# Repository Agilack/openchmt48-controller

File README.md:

# PickNPlace

Réingenierie d'une machine Pick and Place.

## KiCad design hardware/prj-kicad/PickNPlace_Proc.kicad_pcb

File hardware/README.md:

# pcb

Pinout
------

Diagram and table below show the details of boards connectors.

<table>
<tr><th>Connector</th><th>Signal</th><th>Type</th><th>MCU io</th>     <th>&nbsp</th> <th>Connector</th><th>Signal</th><th>Type</th><th>MCU io</th></tr>
<tr><td>J3-1</td><td>Light UP</td><td>NPN Output</td><td>PD10</td>    <td>&nbsp</td> <td>J8-1</td><td>Left nozzle pressure</td><td>Analog IN</td><td>PC5</td></tr>
<tr><td>J3-2</td><td>Light Down</td><td>NPN Output</td><td>PD9</td>   <td>&nbsp</td> <td>J8-2</td><td>Right nozzle pressure</td><td>Analog IN</td><td>PC4</td></tr>
<tr><td>J3-3</td><td>Valve Left</td><td>NPN Output</td><td>PD8</td>   <td>&nbsp</td> <td>J9-4</td><td>X-axis zero switch</td><td>Dry Contact</td><td>PC10</td></tr>
<tr><td>J3-4</td><td>Valve Right</td><td>NPN Output</td><td>PB15</td> <td>&nbsp</td> <td>J9-5</td><td>Y-axis zero switch</td><td>Dry Contact</td><td>PC11</td></tr>
<tr><td>J3-6</td><td>Needle</td><td>NPN Output</td><td>PB14</td>      <td>&nbsp</td> <td>&nbsp</td><td>&nbsp</td><td>&nbsp</td><td>&nbsp</td></tr>
<tr><td>J5-1</td><td>Pump Blow</td><td>NPN Output</td><td>PD12</td>   <td>&nbsp</td> <td>&nbsp</td><td>&nbsp</td><td>&nbsp</td><td>&nbsp</td></tr>
<tr><td>J5-4</td><td>Pump Vaccum</td><td>NPN Output</td><td>PD13</td> <td>&nbsp</td> <td>&nbsp</td><td>&nbsp</td><td>&nbsp</td><td>&nbsp</td></tr>
<tr><td>J6-4</td><td>Y encoder B-</td><td>Digital IN</td><td>PB13</td><td>&nbsp</td> <td>J1-4</td><td>X encoder B-</td><td>Digital IN</td><td>PE15</td></tr>
<tr><td>J6-5</td><td>Y encoder B+</td><td>Digital IN</td><td>PB13</td><td>&nbsp</td> <td>J1-5</td><td>X encoder B+</td><td>Digital IN</td><td>PE15</td></tr>
<tr><td>J6-6</td><td>Y encoder A-</td><td>Digital IN</td><td>PB12</td><td>&nbsp</td> <td>J1-6</td><td>X encoder A-</td><td>Digital IN</td><td>PE14</td></tr>
<tr><td>J6-7</td><td>Y encoder A+</td><td>Digital IN</td><td>PB12</td><td>&nbsp</td> <td>J1-7</td><td>X encoder A+</td><td>Digital IN</td><td>PE14</td></tr>
<tr><td>J12-1</td><td>Reels Step clock</td><td>Digital Output</td><td>PA2</td> <td>&nbsp</td> <td>J11-1</td><td>Nozzle 2 rotation clock</td><td>Digital Output</td><td>PB0</td>
<tr><td>J12-2</td><td>Reels Direction</td><td>Digital Output</td><td>PC2</td>  <td>&nbsp</td> <td>J11-2</td><td>Nozzle 2 rotation direction</td><td>Digital Output</td><td>PF14</td>
<tr><td>J12-3</td><td>Y step clock</td><td>Digital Output</td><td>PA1</td>     <td>&nbsp</td> <td>J11-3</td><td>Nozzle 1 rotation clock</td><td>Digital Output</td><td>PA7</td>
<tr><td>J12-4</td><td>Y Direction</td><td>Digital Output</td><td>PC1</td>      <td>&nbsp</td> <td>J11-4</td><td>Nozzle 1 rotation direction</td><td>Digital Output</td><td>PF15</td>
<tr><td>J12-5</td><td>X Step clock</td><td>Digital Output</td><td>PA0</td>     <td>&nbsp</td> <td>J11-5</td><td>Nozzle Z clock</td><td>Digital Output</td><td>PA6</td></tr>
<tr><td>J12-6</td><td>X Direction</td><td>Digital Output</td><td>PC0</td>      <td>&nbsp</td> <td>J11-6</td><td>Nozzle Z direction</td><td>Digital Output</td><td>PF13</td></tr>
<tr><td>J12-7</td><td>XYR enable</td><td>Digital Output</td><td>PA4</td>       <td>&nbsp</td> <td>J11-7</td><td>BCD enable</td><td>Digital Output</td><td>PA5</td></tr>
</table>

Changelog
---------

 * rev 0.2
   - Support for pumps control (vaccum and blow)
   - Support for logic outputs (valves, needle, lights)
   - Analog inputs for pressure sensors

 * rev 0.1
   - Support all stepper motors (X, Y, Z, reel, nozzle)
   - Inputs for encoders (X and Y axis)
   - Power supplies for head (7v, 5v)

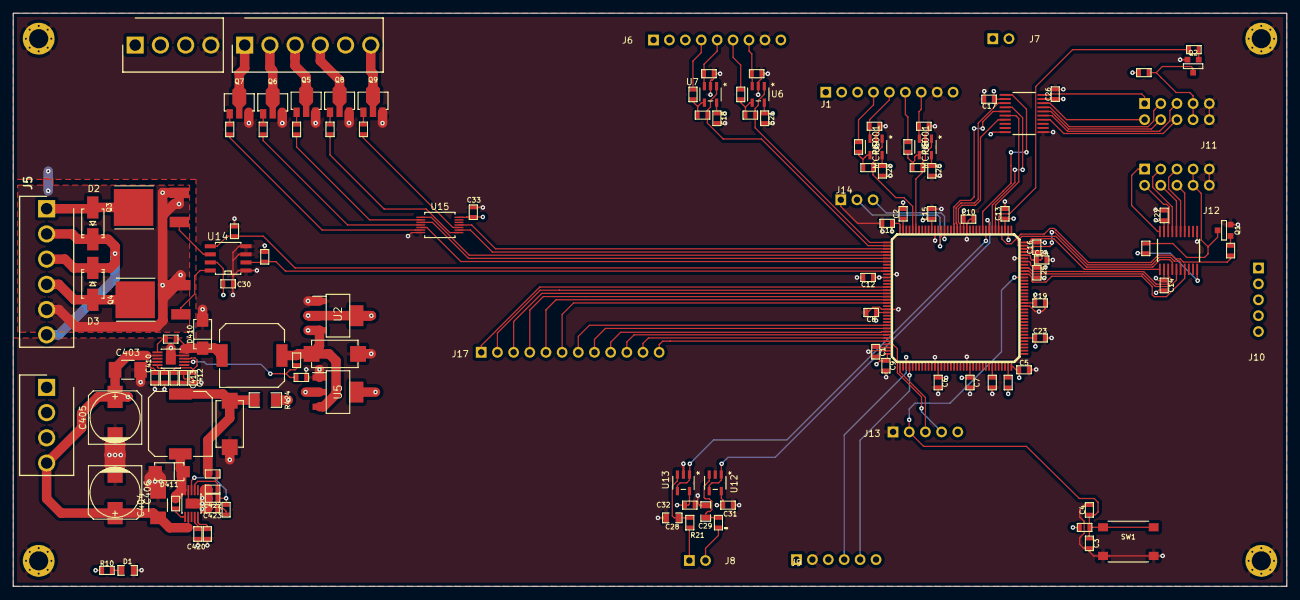
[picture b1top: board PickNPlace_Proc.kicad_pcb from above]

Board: 4 copper layers, 200.0 x 90.0 mm, 136 parts (0 on the bottom side), 124 nets.

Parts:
C1, C2: 2,2uF; SMD0603
C3, C30: 1uF; SMD0603
C4, C5, C6, C7, C8, C9, C10, C11, C12, C13, C14, C15, C16, C17, C18, C19, C20, C21, C22, C23, C24, C25, C26, C27, C31, C32, C33: 100nF; SMD0603
C28, C29: 1uF; SMD0805
C403, C404: 2,2uF; C_1210
C405, C406: 100uF; C_ALU_8x10.5
C410, C420: 10nF; SMD0603
C411, C421: 100nF; C_0603
C412, C422: n/a; SMD0603
C413, C423: 4,7nF; SMD0603
C414, C424: 220uF; C_TPB_D4
D1: LED; SMD0805
D2, D3: S1MLR3; D_SMA
D410, D411: MBRA340; DO214AC
FIX1, FIX2, FIX3, FIX4: CONN_1; FIX
J1, J6: Conn_01x09; 2_50___9pins
J2, J4: Conn_01x04; 3_96__4pins
J3, J5: Conn_01x06; B6P-VH_LF__SN_
J7, J8: Conn_01x02; 2_54___2pins
J9: Conn_01x06; 2_50___6pins
J10: Conn_01x05; 2_50___5pins
J11, J12: Conn_02x05_Odd_Even; 2_54____10pins__2rows
J13: Conn_01x05; 2_54____5pins
J14: Conn_01x03; 2_54___3pins
J17: Conn_01x12; 2_54____12pins
L410, L411: 27uH; I_MSS1048
Q1, Q2: Q_NPN; SOT23-3
Q3, Q4: Q_NMOS; TO-252-2Lead
Q5, Q6, Q7, Q8, Q9: NPN_2SCR533P_HZG; SOT-89
R1, R2, R3, R4, R5, R6, R7, R8, R9, R11, R12, R13, R14, R15, R16, R17, R18, R23, R24: 10k; R_0603
R10: 470; SMD0603
R19, R20, R21, R22: 1k; R_0603
R25, R26, R27, R28, R29: 470; R_0603
R410, R420: 100k; R_0603
R411, R421: 20k; R_0603
R412: 93,1k; R_0603
R413: 12k; R_0603
R422: 47k; R_0603
R423: 15k; R_0603
R424: 0; SMD1206
SW1: SW_PUSH; SW_430152043826
U1: STM32F745ZX; TQFP144
U2, U5: LM1117-5.0; TO261AA-LM1117
U3, U4: TPS54160A; MSOP10p
U6, U7, U8, U9, U12, U13: MCP6001; MCP6001T-I&slash_OT
U10, U11: TXS0108E-RGY; TSSOP20
U14: FAN3225TMX; SOIC-8
U15: SN74LVC07ADGVR; TVSOP-14_SN74LVC07ADGVR_copy

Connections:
+3V3: C5.1, C6.1, C7.1, C8.1, C9.1, C10.1, C11.1, C12.1, C13.1, C14.1, C15.1, C16.1, C17.1, C18.1, C19.1, C20.1, C21.1, C22.1, C23.1, C24.1, C25.1, C31.1, C32.1, C33.1, J13.5, R14.1, R16.1, R19.1, R20.1, R424.2, U1.6, U1.17, U1.30, U1.32, U1.33, U1.39, U1.52, U1.62, U1.72, U1.84, U1.95, U1.108, U1.121, U1.131, U1.144, U6.5, U7.5, U8.5, U9.5, U10.2, U10.10, U11.2, U11.10, U12.5, U13.5, U15.14
+5V: C26.1, C27.1, J4.3, R10.1, U2.2, U10.19, U11.19
+5V_bis: J1.9, J6.9, U5.2
+7V: C30.1, C414.1, J4.2, L410.2, R412.1, U2.3, U5.3, U14.7
+24V_3: D2.1, D3.1, J5.2, J5.3, J5.6
+VIn: C403.1, C404.1, C405.1, C406.1, J2.4, J4.1, U3.2, U4.2
/Power Supply/3V3_SW: C421.2, D411.2, L411.1, U4.10
/Power Supply/V5_SW: C411.2, D410.2, L410.1, U3.10
Add_IO1: J17.1, U1.87
Add_IO2: J17.2, U1.88
Add_IO3: J17.3, U1.89
Add_IO4: J17.4, U1.90
Add_IO5: J17.5, U1.91
Add_IO6: J17.6, U1.92
Add_IO7: J17.7, U1.99
Add_IO8: J17.8, U1.100
Add_IO9: J17.9, U1.101
Add_IO10: J17.10, U1.102
Add_IO11: J17.11, U1.103
Add_IO12: J17.12, U1.104
BCD_EN: J11.7, J11.8, Q2.3, R20.2
BCD_ENABLE: R18.2, U1.41
BLOW_PWM: R23.1, U1.81, U14.5
Downward_light: U1.78, U15.3
GND: C1.2, C2.2, C3.2, C4.2, C5.2, C6.2, C7.2, C8.2, C9.2, C10.2, C11.2, C12.2, C13.2, C14.2, C15.2, C16.2, C17.2, C18.2, C19.2, C20.2, C21.2, C22.2, C23.2, C24.2, C25.2, C26.2, C27.2, C28.2, C29.2, C30.2, C31.2, C32.2, C33.2, C403.2, C404.2, C405.2, C406.2, C410.2, C412.2, C413.2, C414.2, C420.2, C422.2, C423.2, C424.2, D1.2, D410.1, D411.1, FIX1.1, FIX2.1, FIX3.1, FIX4.1, J1.8, J2.3, J4.4, J5.5, J6.8, J9.2, J11.9, J11.10, J12.9, J12.10, J13.1, J14.1, Q1.2, Q2.2, Q3.3, Q4.3, Q5.3, Q6.3, Q7.3, Q8.3, Q9.3, R5.2, R6.2, R7.2, R8.2, R15.2, R23.2, R24.2, R410.2, R413.2, R420.2, R423.2, SW1.1, U1.16, U1.31, U1.38, U1.51, U1.61, U1.83, U1.94, U1.107, U1.120, U1.130, U2.1, U3.9, U3.PAD, U4.9, U4.PAD, U5.1, U6.2, U7.2, U8.2, U9.2, U10.11, U11.11, U12.2, U13.2, U14.1, U14.3, U14.4, U15.7
LEFT_NOZZLE_PRESSURE: U1.45, U13.1, U13.4
Needle: U1.75, U15.11
unnamed: C1.1, U1.106
unnamed: C2.1, U1.71
unnamed: C28.1, R21.2, U13.3
unnamed: C29.1, R22.2, U12.3
unnamed: C410.1, U3.4
unnamed: C411.1, U3.1
unnamed: C412.1, R411.1, U3.8
unnamed: C413.1, R411.2
unnamed: C420.1, U4.4
unnamed: C421.1, U4.1
unnamed: C422.1, R421.1, U4.8
unnamed: C423.1, R421.2
unnamed: C424.1, L411.2, R422.1, R424.1
unnamed: D1.1, R10.2
unnamed: J3.1, Q7.2
unnamed: J3.2, Q6.2
unnamed: J3.3, Q5.2
unnamed: J3.4, Q8.2
unnamed: J3.6, Q9.2
unnamed: J8.1, R21.1
unnamed: J8.2, R22.1
unnamed: Q1.1, R17.1
unnamed: Q2.1, R18.1
unnamed: Q3.1, U14.6
unnamed: Q4.1, U14.8
unnamed: Q5.1, R25.1
unnamed: Q6.1, R26.1
unnamed: Q7.1, R27.1
unnamed: Q8.1, R28.1
unnamed: Q9.1, R29.1
unnamed: R1.1, R9.1, U6.4
unnamed: R2.1, R11.1, U7.4
unnamed: R3.1, R12.1, U8.4
unnamed: R4.1, R13.1, U9.4
unnamed: R14.2, U1.143
unnamed: R15.1, U1.138
unnamed: R25.2, U15.2
unnamed: R26.2, U15.4
unnamed: R27.2, U15.6
unnamed: R28.2, U15.8
unnamed: R29.2, U15.10
unnamed: R410.1, U3.5
unnamed: R412.2, R413.1, U3.7
unnamed: R420.1, U4.5
unnamed: R422.2, R423.1, U4.7
Nozzle_CLK_3v3: U1.42, U11.6
Nozzle_CLK_5v: J11.5, U11.15
Nozzle_DIR_3v3: U1.53, U11.7
Nozzle_DIR_5v: J11.6, U11.14
Pump_blow-: D2.2, J5.1, Q3.2
Pump_vacuum-: D3.2, J5.4, Q4.2
RIGHT_NOZZLE_PRESSURE: U1.44, U12.1, U12.4
RST: C3.1, C4.1, J13.2, R16.2, SW1.2, U1.25
RX: J14.3, U1.58
Rot-Noz1_CLK_3v3: U1.43, U11.4
Rot-Noz1_CLK_5v: J11.3, U11.17
Rot-Noz1_DIR_3v3: U1.55, U11.5
Rot-Noz1_DIR_5v: J11.4, U11.16
Rot-Noz2_CLK_3v3: U1.46, U11.1
Rot-Noz2_CLK_5v: J11.1, U11.20
Rot-Noz2_DIR_3v3: U1.54, U11.3
Rot-Noz2_DIR_5v: J11.2, U11.18
Rub_CLK_3v3: U1.36, U10.1
Rub_CLK_5v: J12.1, U10.20
Rub_DIR_3v3: U1.28, U10.3
Rub_DIR_5v: J12.2, U10.18
SWCLK: J13.3, U1.109
SWDIO: J13.4, U1.105
TX: J14.2, U1.59
Upward_light: U1.79, U15.5
VACUUM_PWM: R24.1, U1.82, U14.2
Valve_left: U1.77, U15.1
Valve_right: U1.76, U15.9
XYZ_EN: J12.7, J12.8, Q1.3, R19.2
XYZ_ENABLE: R17.2, U1.40
X_A: R12.2, U1.67, U8.1
X_A+: J1.7, R7.1, U8.3
X_A-: J1.6, R3.2
X_B: R13.2, U1.68, U9.1
X_B+: J1.5, R8.1, U9.3
X_B-: J1.4, R4.2
X_CLK_3v3: U1.34, U10.6
X_CLK_5v: J12.5, U10.15
X_DIR_3v3: U1.26, U10.7
X_DIR_5v: J12.6, U10.14
X_lim: J9.4, U1.111
Y_A: R9.2, U1.73, U6.1
Y_A+: J6.7, R5.1, U6.3
Y_A-: J6.6, R1.2
Y_B: R11.2, U1.74, U7.1
Y_B+: J6.5, R6.1, U7.3
Y_B-: J6.4, R2.2
Y_CLK_3v3: U1.35, U10.4
Y_CLK_5v: J12.3, U10.17
Y_DIR_3v3: U1.27, U10.5
Y_DIR_5v: J12.4, U10.16
Y_lim: J9.5, U1.112

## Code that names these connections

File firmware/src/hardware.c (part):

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    val |= (1 << 3); /* GPIO-D */
    reg_wr((u32)RCC_AHB1ENR, val);
    
    //BLOW_PWM PD12
    reg_clr((u32)GPIOD_MODER, 0x3000000);       //Clear bits 24 and 25
    reg_set((u32)GPIOD_MODER, (2 << 24));    //AF mode

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    reg_set((u32)TIM4_CCMR1, (1 << 3));    //Preload enable
    //reg16_set((u32)TIM4_CCER, (1 << 0));  //Enable CC2

    //VACUUM_PWM PD13
    reg_clr((u32)GPIOD_MODER, 0xC000000);       //Clear bits 26 and 27
    reg_set((u32)GPIOD_MODER, (2 << 26));    //AF mode

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
    reg16_set((u32)TIM3_EGR, (1 << 0));     //Update generation

//NEEDLE INIT on PB14 = TIM12_CH1

    /* Activate GPIO controller(s) */
    val = reg_rd((u32)RCC_AHB1ENR);
    val |= (1 << 1); /* GPIO-B */
    reg_wr((u32)RCC_AHB1ENR, val);
    
    //NEEDLE PB14
    reg_clr((u32)GPIOB_MODER, 0x30000000);       //Clear bits 28 and 29
    reg_set((u32)GPIOB_MODER, (2 << 28));    //AF mode

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    val |= (1 << 5); /* GPIO-F */
    reg_wr((u32)RCC_AHB1ENR, val);

//XYZ_EN PA4
    reg_clr((u32)GPIOA_MODER, 0x300);       //Clear bits 8 and 9
    reg_set((u32)GPIOA_MODER, (1 << 8));    //Output mode

    reg_set((u32)GPIOA_BSRR, (1 << 4));     //PA4 HIGH = ENABLE

//BCD_EN PA5
    reg_clr((u32)GPIOA_MODER, 0xC00);       //Clear bits 10 and 11
    reg_set((u32)GPIOA_MODER, (1 << 10));    //Output mode

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
    reg_set((u32)GPIOF_BSRR, (1 << 15));     //PF15 HIGH = ENABLE

//X_A PE14
    reg_clr((u32)GPIOE_MODER, 0x30000000);     //Clear bits 28 and 29
    reg_set((u32)GPIOE_MODER, (0 << 28));      //Input mode

//X_B PE15
    reg_clr((u32)GPIOE_MODER, 0xC0000000);     //Clear bits 30 and 31
    reg_set((u32)GPIOE_MODER, (0 << 30));      //Input mode

//Y_A PB12
    reg_clr((u32)GPIOB_MODER, 0x3000000);      //Clear bits 24 and 25
    reg_set((u32)GPIOB_MODER, (0 << 24));      //Input mode

//Y_B PB13
    reg_clr((u32)GPIOB_MODER, 0xC000000);     //Clear bits 26 and 27
    reg_set((u32)GPIOB_MODER, (0 << 26));      //Input mode

//X_lim PC10
    reg_clr((u32)GPIOC_MODER, 0x300000);     //Clear bits 20 and 21
    reg_set((u32)GPIOC_MODER, (0 << 20));      //Input mode

//Y_lim PC11
    reg_clr((u32)GPIOC_MODER, 0xC00000);     //Clear bits 22 and 23
    reg_set((u32)GPIOC_MODER, (0 << 22));      //Input mode

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    val |= 0x500000;                            //Pull up on PC10 and PC11
    reg_wr((u32)GPIO_PUPD(GPIOC), val);

//Valve_Right PB15
    reg_clr((u32)GPIOB_MODER, 0xC0000000);     //Clear bits 30 and 31
    reg_set((u32)GPIOB_MODER, (1 << 30));      //Output mode

//Valve_Left PD8
    reg_clr((u32)GPIOD_MODER, 0x30000);     //Clear bits 16 and 17
    reg_set((u32)GPIOD_MODER, (1 << 16));      //Output mode

//Downward_Light PD9
    reg_clr((u32)GPIOD_MODER, 0xC0000);     //Clear bits 18 and 19
    reg_set((u32)GPIOD_MODER, (1 << 18));      //Output mode

//Upward_Light PD10
    reg_clr((u32)GPIOD_MODER, 0x300000);     //Clear bits 20 and 21
    reg_set((u32)GPIOD_MODER, (1 << 20));      //Output mode

//Right_Nozzle_Pressure PC4
    reg_clr((u32)GPIOC_MODER, 0x300);     //Clear bits 8 and 9
    reg_set((u32)GPIOC_MODER, (3 << 8));      //Analog mode

//Left_Nozzle_Pressure PC5
    reg_clr((u32)GPIOC_MODER, 0xC00);     //Clear bits 10 and 11
    reg_set((u32)GPIOC_MODER, (3 << 10));      //Analog mode
}
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    reg_set((u32)ADC1_CR2, (1 << 0));       //Enable ADC1
}

//Setup interruption from the X_A signal (PE14)
static void Setup_X_A_interupt(void)
{
    unsigned long int val;
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    reg_set(EXTI + 0x00, 1 << 14);
}

//Setup interruption for the X_B signal (PE15)
static void Setup_X_B_interupt(void)
{
    unsigned long int val;
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    reg_set(EXTI + 0x00, 1 << 15);
}

//Setup interruption from the Y_A signal (PB12)
static void Setup_Y_A_interupt(void)
{
    unsigned long int val;
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    reg_set(EXTI + 0x00, 1 << 12);
}

//Setup interruption for the Y_B signal (PB13)
static void Setup_Y_B_interupt(void)
{
    unsigned long int val;
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
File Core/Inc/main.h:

/* USER CODE BEGIN Header */
/**
  ******************************************************************************
  * @file           : main.h
  * @brief          : Header for main.c file.
  *                   This file contains the common defines of the application.
  ******************************************************************************
  * @attention
  *
  * <h2><center>&copy; Copyright (c) 2021 STMicroelectronics.
  * All rights reserved.</center></h2>
  *
  * This software component is licensed by ST under BSD 3-Clause license,
  * the "License"; You may not use this file except in compliance with the
  * License. You may obtain a copy of the License at:
  *                        opensource.org/licenses/BSD-3-Clause
  *
  ******************************************************************************
  */
/* USER CODE END Header */

/* Define to prevent recursive inclusion -------------------------------------*/
#ifndef __MAIN_H
#define __MAIN_H

#ifdef __cplusplus
extern "C" {
#endif

/* Includes ------------------------------------------------------------------*/
#include "stm32f7xx_hal.h"

/* Private includes ----------------------------------------------------------*/
/* USER CODE BEGIN Includes */

/* USER CODE END Includes */

/* Exported types ------------------------------------------------------------*/
/* USER CODE BEGIN ET */

/* USER CODE END ET */

/* Exported constants --------------------------------------------------------*/
/* USER CODE BEGIN EC */

/* USER CODE END EC */

/* Exported macro ------------------------------------------------------------*/
/* USER CODE BEGIN EM */

/* USER CODE END EM */

/* Exported functions prototypes ---------------------------------------------*/
void Error_Handler(void);

/* USER CODE BEGIN EFP */

/* USER CODE END EFP */

/* Private defines -----------------------------------------------------------*/
#define X_DIR_Pin GPIO_PIN_0
#define X_DIR_GPIO_Port GPIOC
#define Y_DIR_Pin GPIO_PIN_1
#define Y_DIR_GPIO_Port GPIOC
#define X_CLK_Pin GPIO_PIN_0
#define X_CLK_GPIO_Port GPIOA
#define Y_CLK_Pin GPIO_PIN_1
#define Y_CLK_GPIO_Port GPIOA
#define XYZ_ENABLE_Pin GPIO_PIN_4
#define XYZ_ENABLE_GPIO_Port GPIOA
#define BCD_ENABLE_Pin GPIO_PIN_5
#define BCD_ENABLE_GPIO_Port GPIOA
#define NOZZLE_CLK_Pin GPIO_PIN_6
#define NOZZLE_CLK_GPIO_Port GPIOA
#define NOZZLE_DIR_Pin GPIO_PIN_13
#define NOZZLE_DIR_GPIO_Port GPIOF
#define X_A_Pin GPIO_PIN_14
#define X_A_GPIO_Port GPIOE
#define X_B_Pin GPIO_PIN_15
#define X_B_GPIO_Port GPIOE
#define Y_A_Pin GPIO_PIN_12
#define Y_A_GPIO_Port GPIOB
#define Y_B_Pin GPIO_PIN_13
#define Y_B_GPIO_Port GPIOB
#define X_Lim_Pin GPIO_PIN_10
#define X_Lim_GPIO_Port GPIOC
#define Y_Lim_Pin GPIO_PIN_11
#define Y_Lim_GPIO_Port GPIOC
/* USER CODE BEGIN Private defines */

/* USER CODE END Private defines */

#ifdef __cplusplus
}
#endif

#endif /* __MAIN_H */

/************************ (C) COPYRIGHT STMicroelectronics *****END OF FILE****/

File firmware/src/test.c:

/**
 * @file  test.c
 * @brief contains test functions to test the hardware of pnp
 *
 * @author Axel Paolillo <axel.paolillo@agilack.fr>
 * @copyright Agilack (c) 2021
 *
 * @page License
 * This firmware is free software: you can redistribute it and/or modify it
 * under the terms of the GNU Lesser General Public License version 3 as
 * published by the Free Software Foundation. You should have received a
 * copy of the GNU Lesser General Public License along with this program,
 * see LICENSE.md file for more details.
 * This program is distributed WITHOUT ANY WARRANTY.
 */

#include "types.h"
#include "hardware.h"
#include "pnp.h"
#include "test.h"
//#include "rtos/include/FreeRTOS.h"
#include "uart.h"
//#include "main.h"
#include "valve.h"
#include "light.h"

#define OFF 0
#define ON  1


void delay_rtos(int ms);

void adc_test(void)
{
    uint adc_val=0;

    while(1)
    {
        delay_rtos(500);
        reg_set((u32)ADC1_CR2, (1 << 30));      //START CONVERSION
        while (!(reg_rd(ADC1_SR) & (1 << 1)));  //Waiting for end of conversion
        adc_val = reg_rd(ADC1_DR);
        uart_puts("\r\n ADC VAL = ");
        uart_putdec(adc_val);
    }
}

void pump_vacuum_blow_test(void)
{
    reg16_set((u32)TIM4_CCER, (1 << 0));        //Enable BLOW PWM

    //reg16_clr((u32)TIM4_CCER, (1 << 0));        //Disable BLOW PWM

    reg16_set((u32)TIM4_CCER, (1 << 4));        //Enable Vacuum PWM

    //reg16_clr((u32)TIM4_CCER, (1 << 4));        //Disable BLOW PWM
}

void nozzle_test(void)
{
    reg16_set((u32)TIM3_CCER, (1 << 0));        //Enable Nozzle CLK PWM

    //reg16_clr((u32)TIM3_CCER, (1 << 0));        //Disable Nozzle CLK PWM

    reg16_set((u32)TIM3_CCER, (1 << 4));        //Enable Rot-Noz1-CLK PWM

    //reg16_clr((u32)TIM3_CCER, (1 << 4));        //Disable Rot-Noz1-CLK PWM

    reg16_set((u32)TIM3_CCER, (1 << 8));        //Enable Rot-Noz2-CLK PWM

    //reg16_clr((u32)TIM3_CCER, (1 << 8));        //Disable Rot-Noz2-CLK PWM
}

void valve_light_test(void)
{
    while(1)
    {
        valve_right(ON);
        valve_left(ON);
        down_light(ON);
        up_light(ON);
        delay_rtos(3000);
        valve_right(OFF);
        valve_left(OFF);
        down_light(OFF);
        up_light(OFF);
        delay_rtos(3000);
    }
}

void test_hw_encoder(void)
{
    delay_rtos(200);
    if ((reg_rd(GPIO_IDR(GPIOA)) & (1 << 11)) == 0)
    {
        reg_clr((u32)TIM_CNT(TIM1), 0xFFFF);
        uart_puts("Encoder value reset !\r\n");
    }
    uart_puts("Encoder value : ");
    uart_putdec(reg_rd((u32)TIM_CNT(TIM1)));
    uart_puts("\r\n");
}

void encoder_init(void)     //WIP
{
    u32 val;

    reg_set((u32)RCC_APB2ENR, (1 << 14));    //Enbale SYSCFG
    reg_set((u32)RCC_APB2ENR, (1 << 0));     //TIM1 enable

//Add_IO8 PA8
    reg_clr((u32)GPIOA_MODER, 0x30000);       //Clear bits 16 and 17
    reg_set((u32)GPIOA_MODER, (2 << 16));    //AF mode

    val = reg_rd((u32)GPIOA_AFRH);
    val |= (1 << 0);                    //AF1 (TIM1_CH1) on PA8
    reg_wr((u32)GPIOA_AFRH, val);

//Add_IO9 PA9
    reg_clr((u32)GPIOA_MODER, 0xC0000);       //Clear bits 18 and 19
    reg_set((u32)GPIOA_MODER, (2 << 18));    //AF mode

    val = reg_rd((u32)GPIOA_AFRH);
    val |= (1 << 4);                    //AF1 (TIM1_CH2) on PA9
    reg_wr((u32)GPIOA_AFRH, val);

    val = reg_rd((u32)GPIO_PUPD(GPIOA));
    val &= ~(0xF0000);                        //Clear bits 16 to 19
    val |= 0x50000;                            //Pull down on PA8 and PA9
    reg_wr((u32)GPIO_PUPD(GPIOA), val);

//Add_IO11 PA11    Encoder pusher button
    reg_clr((u32)GPIOA_MODER, 0xC00000);       //Clear bits 22 and 23
    reg_set((u32)GPIOA_MODER, (0 << 22));    //Input mode


    reg_set((u32)TIM1_CCMR1, (1 << 0));      //Channel 1 as TI1
    reg_set((u32)TIM1_CCMR1, (1 << 8));      //Channel 2 as TI2

    reg_set((u32)TIM1_SMCR, (3 << 0));        //Encoder mode 3
    reg_set((u32)TIM1_CR1, (1 << 0));        //Enable
}

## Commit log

2021-04-29 Iteration n°1 : Control X motor, its direction and its speed.
2021-05-07 Iteration n°2 : Control X position, verification via encoder
2021-07-06 Transition from nucleo to custom board
2021-07-06 KiCad schematics and routing
2021-11-17 Drop STM32Cube code, create bare-metal firmware skeleton
2021-11-18 Free RTOS implementation, first task created, LED blink
2021-11-19 PWM test (WIP)
2021-11-19 Firet PWM test works on PnP machine, head goes back and forth
2021-12-24 Test UART RX interruptions
2021-12-28 =ADD: Command support
2021-12-31 add encoder interrupt (WIP)
2022-08-25 Update see details : -Uart in seperate file -More arrows control on terminal -WIP state machine architecture -Set motor speed via PWM period -Functions to test nozzle movements (vertical and rotation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
2022-09-02 Hardware update (rev2) Pumps, valve, pressure sensors, light, needle + fix enable on lvl shifter
2022-10-13 Update to control new hardware, see details : -Added ADC init and read (polling for now) -Added PMW init and control for vaccum and blow pumps and needle -Updated nozzle clocks from regular outputs t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
2022-10-26 HW: Add picture of the PCB rev 0.2
2022-10-29 HW: Update doc, add diagram and table of board connectors pinout

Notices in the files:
parts and their libraries:
Copyright 2016 Accelerated Designs. All rights reserved.
